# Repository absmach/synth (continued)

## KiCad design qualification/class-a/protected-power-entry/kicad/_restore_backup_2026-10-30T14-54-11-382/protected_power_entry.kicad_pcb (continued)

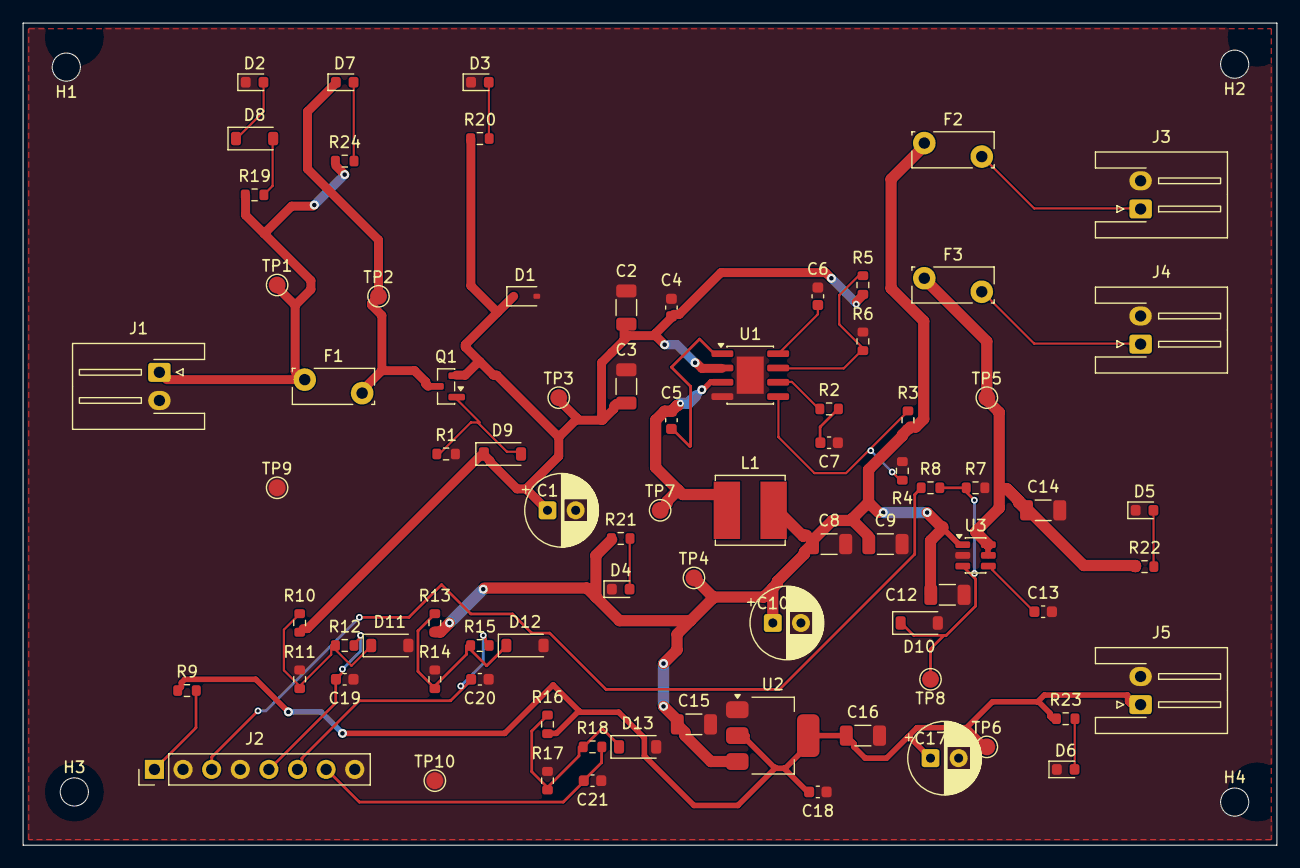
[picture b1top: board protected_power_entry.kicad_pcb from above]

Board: 2 copper layers, 111.3 x 73.0 mm, 84 parts (0 on the bottom side), 34 nets.

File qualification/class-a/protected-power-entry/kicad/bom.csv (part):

refdes,value,kind,description,kicad_symbol,kicad_footprint,lcsc_pn,mpn
C1,100uF 25V,capacitor,"100µF 25V aluminium electrolytic, radial through-hole, polarised",Device:C_Polarized,Capacitor_THT:CP_Radial_D6.3mm_P2.50mm,,
C10,100uF 25V,capacitor,"100µF 25V aluminium electrolytic, radial through-hole, polarised",Device:C_Polarized,Capacitor_THT:CP_Radial_D6.3mm_P2.50mm,,
C12,10uF 10V,capacitor,"Generic 1206 ceramic capacitor, any value",Device:C,Capacitor_SMD:C_1206_3216Metric,,
C13,2.2nF,capacitor,"Generic 0603 MLCC, X7R/X5R, any value",Device:C,Capacitor_SMD:C_0603_1608Metric,,
C14,22uF 10V,capacitor,"Generic 1206 ceramic capacitor, any value",Device:C,Capacitor_SMD:C_1206_3216Metric,,
C15,10uF 10V,capacitor,"Generic 1206 ceramic capacitor, any value",Device:C,Capacitor_SMD:C_1206_3216Metric,,
C16,10uF 10V,capacitor,"Generic 1206 ceramic capacitor, any value",Device:C,Capacitor_SMD:C_1206_3216Metric,,
C17,100uF 25V,capacitor,"100µF 25V aluminium electrolytic, radial through-hole, polarised",Device:C_Polarized,Capacitor_THT:CP_Radial_D6.3mm_P2.50mm,,
C18,100nF,capacitor,"Generic 0603 MLCC, X7R/X5R, any value",Device:C,Capacitor_SMD:C_0603_1608Metric,,
C19,100nF,capacitor,"Generic 0603 MLCC, X7R/X5R, any value",Device:C,Capacitor_SMD:C_0603_1608Metric,,
C2,10uF 25V,capacitor,"Generic 1206 ceramic capacitor, any value",Device:C,Capacitor_SMD:C_1206_3216Metric,,
C20,100nF,capacitor,"Generic 0603 MLCC, X7R/X5R, any value",Device:C,Capacitor_SMD:C_0603_1608Metric,,
C21,100nF,capacitor,"Generic 0603 MLCC, X7R/X5R, any value",Device:C,Capacitor_SMD:C_0603_1608Metric,,
C3,10uF 25V,capacitor,"Generic 1206 ceramic capacitor, any value",Device:C,Capacitor_SMD:C_1206_3216Metric,,
C4,100nF,capacitor,"Generic 0603 MLCC, X7R/X5R, any value",Device:C,Capacitor_SMD:C_0603_1608Metric,,
C5,10nF,capacitor,"Generic 0603 MLCC, X7R/X5R, any value",Device:C,Capacitor_SMD:C_0603_1608Metric,,
C6,100nF,capacitor,"Generic 0603 MLCC, X7R/X5R, any value",Device:C,Capacitor_SMD:C_0603_1608Metric,,
C7,2.2nF,capacitor,"Generic 0603 MLCC, X7R/X5R, any value",Device:C,Capacitor_SMD:C_0603_1608Metric,,
C8,22uF 10V,capacitor,"Generic 1206 ceramic capacitor, any value",Device:C,Capacitor_SMD:C_1206_3216Metric,,
C9,22uF 10V,capacitor,"Generic 1206 ceramic capacitor, any value",Device:C,Capacitor_SMD:C_1206_3216Metric,,
D1,(no value),diode,"5V unidirectional TVS diode, SOD-123 — ESD protection",Device:D_TVS,Diode_SMD:D_SOD-323,,
D10,(no value),diode,"5.1V Zener diode, SOD-123",Device:D_Zener,Diode_SMD:D_SOD-123,,
D11,BZT52C3V3,diode,"BZT52C3V3 3.3 V +/-5 % 500 mW zener diode, SOD-123 (clamp for the ADC sample lines). Vz 3.1 to 3.5 V (nominal 3.3 V) at Izt 5 mA; check against the Diodes Inc. datasheet. No LCSC number asserted.",Device:D_Zener,Diode_SMD:D_SOD-123,,BZT52C3V3
D12,BZT52C3V3,diode,"BZT52C3V3 3.3 V +/-5 % 500 mW zener diode, SOD-123 (clamp for the ADC sample lines). Vz 3.1 to 3.5 V (nominal 3.3 V) at Izt 5 mA; check against the Diodes Inc. datasheet. No LCSC number asserted.",Device:D_Zener,Diode_SMD:D_SOD-123,,BZT52C3V3
D13,BZT52C3V3,diode,"BZT52C3V3 3.3 V +/-5 % 500 mW zener diode, SOD-123 (clamp for the ADC sample lines). Vz 3.1 to 3.5 V (nominal 3.3 V) at Izt 5 mA; check against the Diodes Inc. datasheet. No LCSC number asserted.",Device:D_Zener,Diode_SMD:D_SOD-123,,BZT52C3V3
D2,(no value),diode,"White surface-mount LED, 0603",Device:LED,LED_SMD:LED_0603_1608Metric,,
D3,(no value),diode,"Blue surface-mount LED, 0603",Device:LED,LED_SMD:LED_0603_1608Metric,,
D4,LTST-C190KGKT,diode,"Lite-On LTST-C190KGKT green AlInGaP LED, 0603, Vf 1.9 to 2.4V at 20mA",Device:LED,LED_SMD:LED_0603_1608Metric,,LTST-C190KGKT
D5,0603-GREEN,diode,"Green LED, 0603 package, ~2.2V Vf",Device:LED,LED_SMD:LED_0603_1608Metric,C72043,0603-GREEN
D6,(no value),diode,"Amber surface-mount LED, 0603",Device:LED,LED_SMD:LED_0603_1608Metric,,
D7,LTST-C190KRKT,diode,"Lite-On LTST-C190KRKT red AlInGaP LED, 0603, Vf 1.6 to 2.4V at 20mA",Device:LED,LED_SMD:LED_0603_1608Metric,,LTST-C190KRKT
D8,1N5819HW-7-F,diode,"Diodes Inc. 1N5819HW-7-F, 40 V 1 A Schottky diode, SOD-123, low forward voltage",Device:D_Schottky,Diode_SMD:D_SOD-123,C82544,1N5819HW-7-F
D9,(no value),diode,"5.1V Zener diode, SOD-123",Device:D_Zener,Diode_SMD:D_SOD-123,,
F1,(no value),fuse,"Resettable polyfuse (PPTC), 2-pin",Device:Polyfuse,Fuse:Fuse_Bourns_MF-RG300,,
F2,(no value),fuse,"Resettable polyfuse (PPTC), 2-pin",Device:Polyfuse,Fuse:Fuse_Bourns_MF-RG300,,
F3,(no value),fuse,"Resettable polyfuse (PPTC), 2-pin",Device:Polyfuse,Fuse:Fuse_Bourns_MF-RG300,,
H1,(no value),mounting_hole,M2.5 non-plated mounting hole (NPTH) for a board corner,Mechanical:MountingHole,MountingHole:MountingHole_2.5mm,,
H2,(no value),mounting_hole,M2.5 non-plated mounting hole (NPTH) for a board corner,Mechanical:MountingHole,MountingHole:MountingHole_2.5mm,,
H3,(no value),mounting_hole,M2.5 non-plated mounting hole (NPTH) for a board corner,Mechanical:MountingHole,MountingHole:MountingHole_2.5mm,,
H4,(no value),mounting_hole,M2.5 non-plated mounting hole (NPTH) for a board corner,Mechanical:MountingHole,MountingHole:MountingHole_2.5mm,,
J1,(no value),connector,"JST XH-series 2-pin wire-to-board connector, 2.0mm pitch",Connector_Generic:Conn_01x02,Connector_JST:JST_XH_S2B-XH-A-1_1x02_P2.50mm_Horizontal,,
J2,M20-9990846,connector,"Harwin M20-9990846 1x8 through-hole pin header, 2.54 mm pitch, vertical, 3 A per contact",Connector_Generic:Conn_01x08,Connector_PinHeader_2.54mm:PinHeader_1x08_P2.54mm_Vertical,,M20-9990846
J3,(no value),connector,"JST XH-series 2-pin wire-to-board connector, 2.0mm pitch",Connector_Generic:Conn_01x02,Connector_JST:JST_XH_S2B-XH-A-1_1x02_P2.50mm_Horizontal,,
J4,(no value),connector,"JST XH-series 2-pin wire-to-board connector, 2.0mm pitch",Connector_Generic:Conn_01x02,Connector_JST:JST_XH_S2B-XH-A-1_1x02_P2.50mm_Horizontal,,
J5,(no value),connector,"JST XH-series 2-pin wire-to-board connector, 2.0mm pitch",Connector_Generic:Conn_01x02,Connector_JST:JST_XH_S2B-XH-A-1_1x02_P2.50mm_Horizontal,,
L1,SRN6045TA-100M,inductor,"Bourns SRN6045TA-100M 10 uH semi-shielded power inductor, 6.0x6.0x4.2 mm. Datasheet at 25 C: DCR 52 mOhm +/-20 %, Irms 3.2 A (40 C rise), Isat 4.6 A (30 % inductance drop), SRF 25 MHz.",Device:L,Inductor_SMD:L_Bourns_SRN6045TA,,SRN6045TA-100M
Q1,(no value),transistor,"Vishay Si2301 P-channel power MOSFET, SOT-23",Transistor_FET:Si2301CDS,Package_TO_SOT_SMD:SOT-23,,
R1,47k,resistor,"Generic 0603 thick-film resistor, any value",Device:R_US,Resistor_SMD:R_0603_1608Metric,,
R10,10k,resistor,"Generic 0603 thick-film resistor, any value",Device:R_US,Resistor_SMD:R_0603_1608Metric,,
R11,2k,resistor,"Generic 0603 thick-film resistor, any value",Device:R_US,Resistor_SMD:R_0603_1608Metric,,
R12,1k,resistor,"Generic 0603 thick-film resistor, any value",Device:R_US,Resistor_SMD:R_0603_1608Metric,,
R13,10k,resistor,"Generic 0603 thick-film resistor, any value",Device:R_US,Resistor_SMD:R_0603_1608Metric,,
R14,10k,resistor,"Generic 0603 thick-film resistor, any value",Device:R_US,Resistor_SMD:R_0603_1608Metric,,
R15,1k,resistor,"Generic 0603 thick-film resistor, any value",Device:R_US,Resistor_SMD:R_0603_1608Metric,,
R16,10k,resistor,"Generic 0603 thick-film resistor, any value",Device:R_US,Resistor_SMD:R_0603_1608Metric,,
R17,10k,resistor,"Generic 0603 thick-film resistor, any value",Device:R_US,Resistor_SMD:R_0603_1608Metric,,
R18,1k,resistor,"Generic 0603 thick-film resistor, any value",Device:R_US,Resistor_SMD:R_0603_1608Metric,,
R19,3k,resistor,"Generic 0603 thick-film resistor, any value",Device:R_US,Resistor_SMD:R_0603_1608Metric,,
R2,10k,resistor,"Generic 0603 thick-film resistor, any value",Device:R_US,Resistor_SMD:R_0603_1608Metric,,
R20,3.3k,resistor,"Generic 0603 thick-film resistor, any value",Device:R_US,Resistor_SMD:R_0603_1608Metric,,
R21,1k,resistor,"Generic 0603 thick-film resistor, any value",Device:R_US,Resistor_SMD:R_0603_1608Metric,,
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
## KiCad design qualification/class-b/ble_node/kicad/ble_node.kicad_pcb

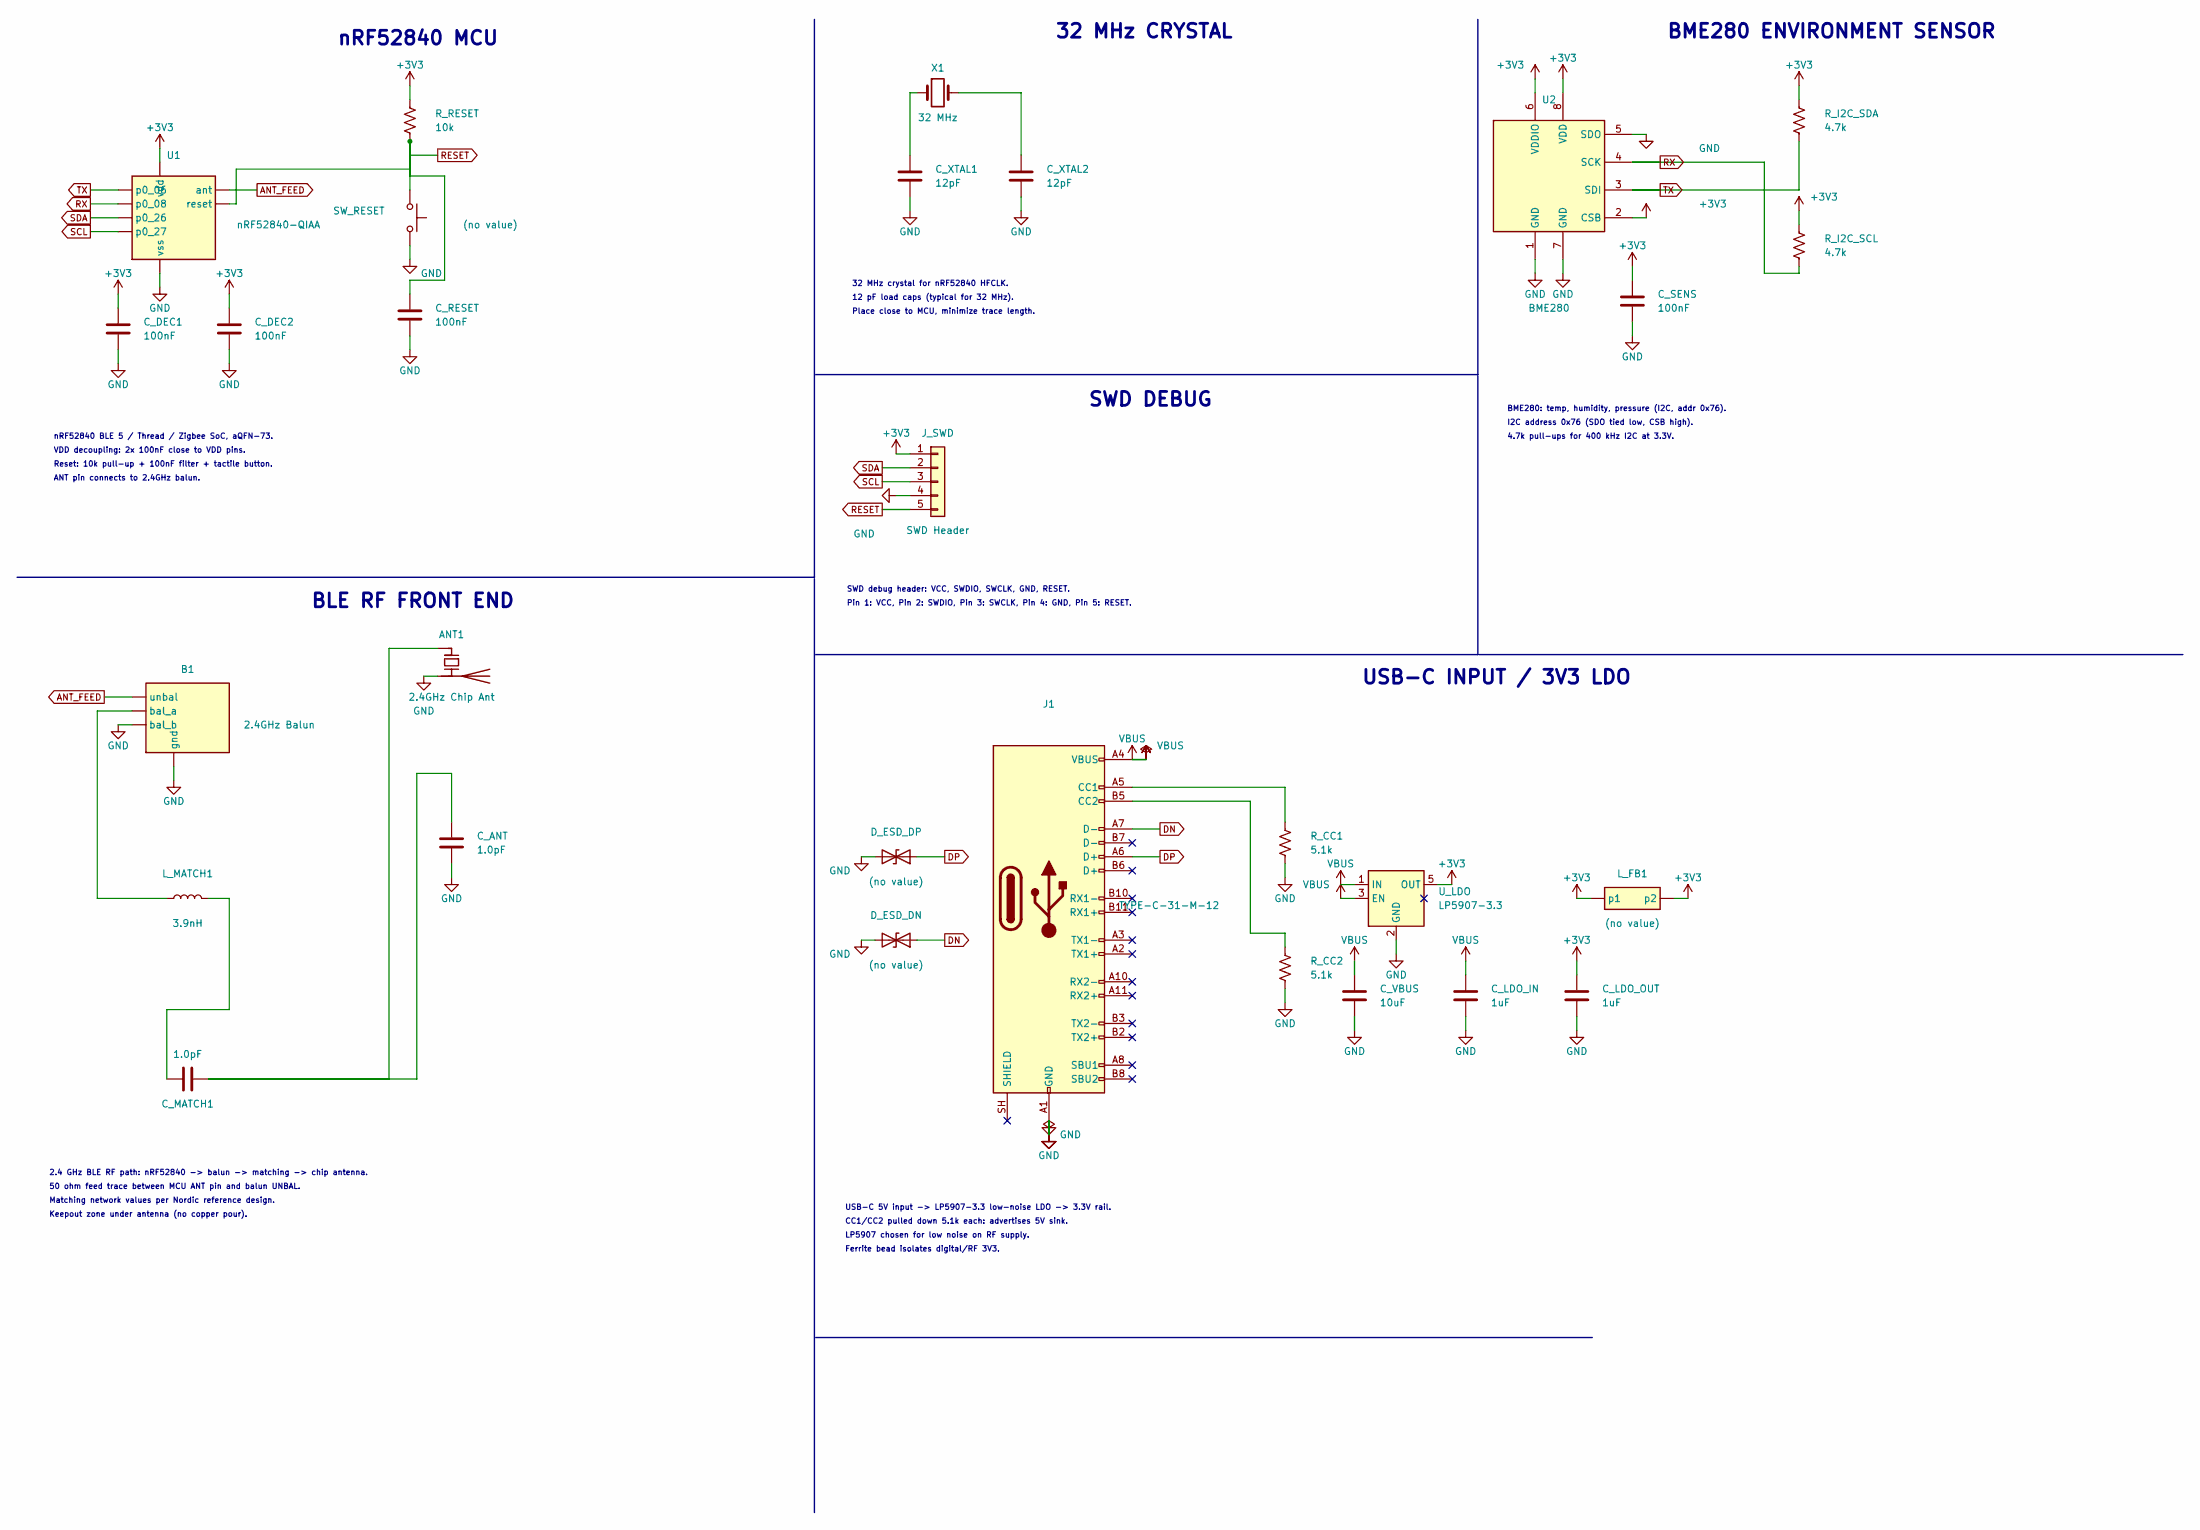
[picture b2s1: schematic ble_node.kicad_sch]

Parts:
ANT1: 2.4GHz Chip Ant; Johanson_2450AT43F0100; MPN 2450AT43F0100E; LCSC C17192881
B1: 2.4GHz Balun; Balun_Johanson_0896BM15A0001; MPN 2450BL15B100
C_ANT: 1.0pF; C_0402_1005Metric
C_DEC1, C_DEC2: 100nF; C_0603_1608Metric
C_LDO_IN: 1uF; C_0603_1608Metric
C_LDO_OUT: 1uF; C_0603_1608Metric
C_MATCH1: 1.0pF; C_0402_1005Metric
C_RESET: 100nF; C_0603_1608Metric
C_SENS: 100nF; C_0603_1608Metric
C_VBUS: 10uF; C_0805_2012Metric
C_XTAL1, C_XTAL2: 12pF; C_0603_1608Metric
D_ESD_DN: (no value); D_SOD-323
D_ESD_DP: (no value); D_SOD-323
J1: TYPE-C-31-M-12; USB_C_Receptacle_HRO_TYPE-C-31-M-12; MPN TYPE-C-31-M-12; LCSC C165948
J_SWD: SWD Header; PinHeader_1x05_P2.54mm_Vertical
L_FB1: (no value); L_0603_1608Metric
L_MATCH1: 3.9nH; L_0402_1005Metric
R_CC1, R_CC2: 5.1k; R_0603_1608Metric
R_I2C_SCL, R_I2C_SDA: 4.7k; R_0603_1608Metric
R_RESET: 10k; R_0603_1608Metric
SW_RESET: (no value); SW_SPST_PTS645Sx43SMTR92
U1: nRF52840-QIAA; Nordic_AQFN-73-1EP_7x7mm_P0.5mm; MPN NRF52840-QIAA-R; LCSC C190794
U2: BME280; Bosch_LGA-8_2.5x2.5mm_P0.65mm_ClockwisePinNumbering; MPN BME280; LCSC C92489
U_LDO: LP5907-3.3; SOT-23-5; MPN LP5907MFX-3.3; LCSC C83437
X1: 32 MHz; Crystal_SMD_3225-4Pin_3.2x2.5mm

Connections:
+3V3: C_DEC1.1, C_DEC2.1, C_LDO_OUT.1, C_SENS.1, J_SWD.1, L_FB1.1 (p1), L_FB1.2 (p2), R_I2C_SCL.2, R_I2C_SDA.2, R_RESET.1, U1.A22 (vdd), U2.2 (CSB), U2.6 (VDDIO), U2.8 (VDD), U_LDO.5 (OUT)
ANT_FEED: B1.1 (unbal), U1.H23 (ant)
GND: ANT1.2 (PCB_Trace), B1.3 (bal_b), B1.4 (gnd), C_ANT.2, C_DEC1.2, C_DEC2.2, C_LDO_IN.2, C_LDO_OUT.2, C_RESET.2, C_SENS.2, C_VBUS.2, C_XTAL1.2, C_XTAL2.2, D_ESD_DN.2 (A2), D_ESD_DP.2 (A2), J1.A1 (GND), J1.A12 (GND), J1.B1 (GND), J1.B12 (GND), J1.SH (SHIELD), J_SWD.4, R_CC1.2, R_CC2.2, SW_RESET.2, U1.B7 (vss), U2.1 (GND), U2.5 (SDO), U2.7 (GND), U_LDO.2 (GND)
net_0: C_LDO_IN.1, C_VBUS.1, J1.A4 (VBUS), J1.A9 (VBUS), J1.B4 (VBUS), J1.B9 (VBUS), U_LDO.1 (IN), U_LDO.3 (EN)
net_3: J1.A5 (CC1), R_CC1.1
net_4: J1.B5 (CC2), R_CC2.1
net_5: D_ESD_DP.1 (A1), J1.A6 (D+), J1.B6 (D+)
net_6: D_ESD_DN.1 (A1), J1.A7 (D-), J1.B7 (D-)
net_7: C_RESET.1, J_SWD.5, R_RESET.2, SW_RESET.1, U1.AC13 (reset)
net_8: C_XTAL1.1, X1.1
net_9: C_XTAL2.1, X1.2
net_10: B1.2 (bal_a), L_MATCH1.1
net_11: C_MATCH1.1, L_MATCH1.2
net_12: ANT1.1 (FEED), C_ANT.1, C_MATCH1.2
net_13: R_I2C_SDA.1, U1.L1 (p0_06), U2.3 (SDI)
net_14: R_I2C_SCL.1, U1.N1 (p0_08), U2.4 (SCK)
net_15: J_SWD.2, U1.G1 (p0_26)
net_16: J_SWD.3, U1.H2 (p0_27)

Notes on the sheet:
USB-C INPUT / 3V3 LDO
nRF52840 MCU
32 MHz CRYSTAL
BLE RF FRONT END
BME280 ENVIRONMENT SENSOR
SWD DEBUG
USB-C 5V input -> LP5907-3.3 low-noise LDO -> 3.3V rail.
CC1/CC2 pulled down 5.1k each: advertises 5V sink.
LP5907 chosen for low noise on RF supply.
Ferrite bead isolates digital/RF 3V3.
nRF52840 BLE 5 / Thread / Zigbee SoC, aQFN-73.
VDD decoupling: 2x 100nF close to VDD pins.
Reset: 10k pull-up + 100nF filter + tactile button.
ANT pin connects to 2.4GHz balun.
32 MHz crystal for nRF52840 HFCLK.
12 pF load caps (typical for 32 MHz).
Place close to MCU, minimize trace length.
2.4 GHz BLE RF path: nRF52840 -> balun -> matching -> chip antenna.
50 ohm feed trace between MCU ANT pin and balun UNBAL.
Matching network values per Nordic reference design.
Keepout zone under antenna (no copper pour).
BME280: temp, humidity, pressure (I2C, addr 0x76).
I2C address 0x76 (SDO tied low, CSB high).
4.7k pull-ups for 400 kHz I2C at 3.3V.
SWD debug header: VCC, SWDIO, SWCLK, GND, RESET.
Pin 1: VCC, Pin 2: SWDIO, Pin 3: SWCLK, Pin 4: GND, Pin 5: RESET.

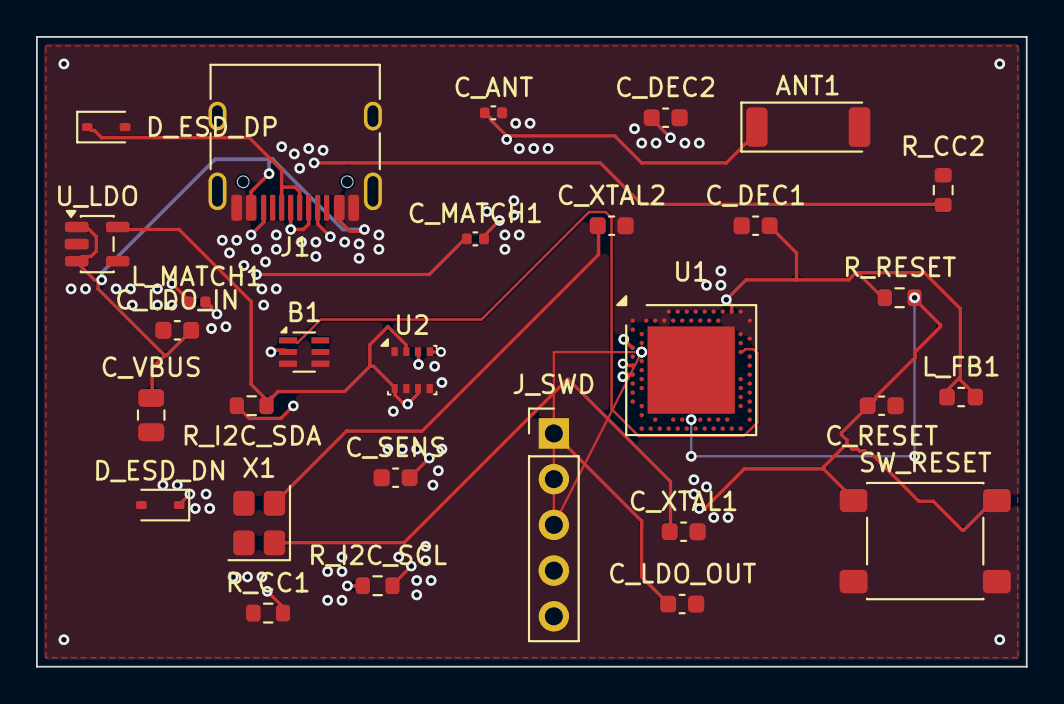
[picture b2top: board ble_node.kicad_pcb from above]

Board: 4 copper layers, 55.0 x 35.0 mm, 29 parts (0 on the bottom side), 18 nets.

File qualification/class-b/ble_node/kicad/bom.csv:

refdes,value,kind,description,kicad_symbol,kicad_footprint,lcsc_pn,mpn
ANT1,2.4GHz Chip Ant,antenna,"Ceramic chip antenna, 2.4 GHz, 1 dBi, SMD",Device:Antenna_Chip,RF_Antenna:Johanson_2450AT43F0100,C17192881,2450AT43F0100E
B1,2.4GHz Balun,filter,"2.4 GHz balun + matching network, integrated SMD",RF_Module:balun_2g4,RF_Converter:Balun_Johanson_0896BM15A0001,,2450BL15B100
C_ANT,1.0pF,capacitor,"Generic 0402 MLCC, X7R/X5R, any value",Device:C,Capacitor_SMD:C_0402_1005Metric,,
C_DEC1,100nF,capacitor,"Generic 0603 MLCC, X7R/X5R, any value",Device:C,Capacitor_SMD:C_0603_1608Metric,,
C_DEC2,100nF,capacitor,"Generic 0603 MLCC, X7R/X5R, any value",Device:C,Capacitor_SMD:C_0603_1608Metric,,
C_LDO_IN,1uF,capacitor,"Generic 0603 MLCC, X7R/X5R, any value",Device:C,Capacitor_SMD:C_0603_1608Metric,,
C_LDO_OUT,1uF,capacitor,"Generic 0603 MLCC, X7R/X5R, any value",Device:C,Capacitor_SMD:C_0603_1608Metric,,
C_MATCH1,1.0pF,capacitor,"Generic 0402 MLCC, X7R/X5R, any value",Device:C,Capacitor_SMD:C_0402_1005Metric,,
C_RESET,100nF,capacitor,"Generic 0603 MLCC, X7R/X5R, any value",Device:C,Capacitor_SMD:C_0603_1608Metric,,
C_SENS,100nF,capacitor,"Generic 0603 MLCC, X7R/X5R, any value",Device:C,Capacitor_SMD:C_0603_1608Metric,,
C_VBUS,10uF,capacitor,"Generic 0805 MLCC, X7R/X5R, any value",Device:C,Capacitor_SMD:C_0805_2012Metric,,
C_XTAL1,12pF,capacitor,"Generic 0603 MLCC, X7R/X5R, any value",Device:C,Capacitor_SMD:C_0603_1608Metric,,
C_XTAL2,12pF,capacitor,"Generic 0603 MLCC, X7R/X5R, any value",Device:C,Capacitor_SMD:C_0603_1608Metric,,
D_ESD_DN,(no value),diode,"USB-line ESD protection (TVS diode array), bidirectional",Device:D_TVS,Diode_SMD:D_SOD-323,,
D_ESD_DP,(no value),diode,"USB-line ESD protection (TVS diode array), bidirectional",Device:D_TVS,Diode_SMD:D_SOD-323,,
J1,TYPE-C-31-M-12,connector,"USB-C receptacle, 24-pin SMD. Modelled here with primary and mirrored power/ground/data pins for full pad coverage.",Connector:USB_C_Receptacle,Connector_USB:USB_C_Receptacle_HRO_TYPE-C-31-M-12,C165948,TYPE-C-31-M-12
J_SWD,SWD Header,connector,"1x5 through-hole pin header, 2.54 mm pitch (SWD); datasheet_url is the product page of the Harwin M20 series, no manufacturer PDF link was verifiable",Connector_Generic:Conn_01x05,Connector_PinHeader_2.54mm:PinHeader_1x05_P2.54mm_Vertical,,
L_FB1,(no value),inductor,"0603 ferrite bead, 600Ω @ 100MHz — EMI suppression",Device:Ferrite_Bead,Inductor_SMD:L_0603_1608Metric,,
L_MATCH1,3.9nH,inductor,"Generic 0402 wirewound inductor, any value",Device:L,Inductor_SMD:L_0402_1005Metric,,
R_CC1,5.1k,resistor,"Generic 0603 thick-film resistor, any value",Device:R_US,Resistor_SMD:R_0603_1608Metric,,
R_CC2,5.1k,resistor,"Generic 0603 thick-film resistor, any value",Device:R_US,Resistor_SMD:R_0603_1608Metric,,
R_I2C_SCL,4.7k,resistor,"Generic 0603 thick-film resistor, any value",Device:R_US,Resistor_SMD:R_0603_1608Metric,,
R_I2C_SDA,4.7k,resistor,"Generic 0603 thick-film resistor, any value",Device:R_US,Resistor_SMD:R_0603_1608Metric,,
R_RESET,10k,resistor,"Generic 0603 thick-film resistor, any value",Device:R_US,Resistor_SMD:R_0603_1608Metric,,
SW_RESET,(no value),switch,Generic SPST tactile button,Switch:SW_Push,Button_Switch_SMD:SW_SPST_PTS645Sx43SMTR92,,
U1,nRF52840-QIAA,mcu,"Nordic nRF52840 ARM Cortex-M4F with BLE 5/Thread/Zigbee, aQFN-73 7x7mm",RF_Module:NRF52840-QIAA,Package_DFN_QFN:Nordic_AQFN-73-1EP_7x7mm_P0.5mm,C190794,NRF52840-QIAA-R
U2,BME280,sensor,"Bosch BME280 temperature/humidity/pressure sensor, I2C/SPI",Sensor:BME280,Package_LGA:Bosch_LGA-8_2.5x2.5mm_P0.65mm_ClockwisePinNumbering,C92489,BME280
U_LDO,LP5907-3.3,regulator,"TI LP5907 3.3V low-noise LDO, 250mA, SOT-23-5",Regulator_Linear:LP5907MFX-3.3,Package_TO_SOT_SMD:SOT-23-5,C83437,LP5907MFX-3.3
X1,32 MHz,crystal,"Generic quartz crystal, 2-pin SMD",Device:Crystal,Crystal:Crystal_SMD_3225-4Pin_3.2x2.5mm,,

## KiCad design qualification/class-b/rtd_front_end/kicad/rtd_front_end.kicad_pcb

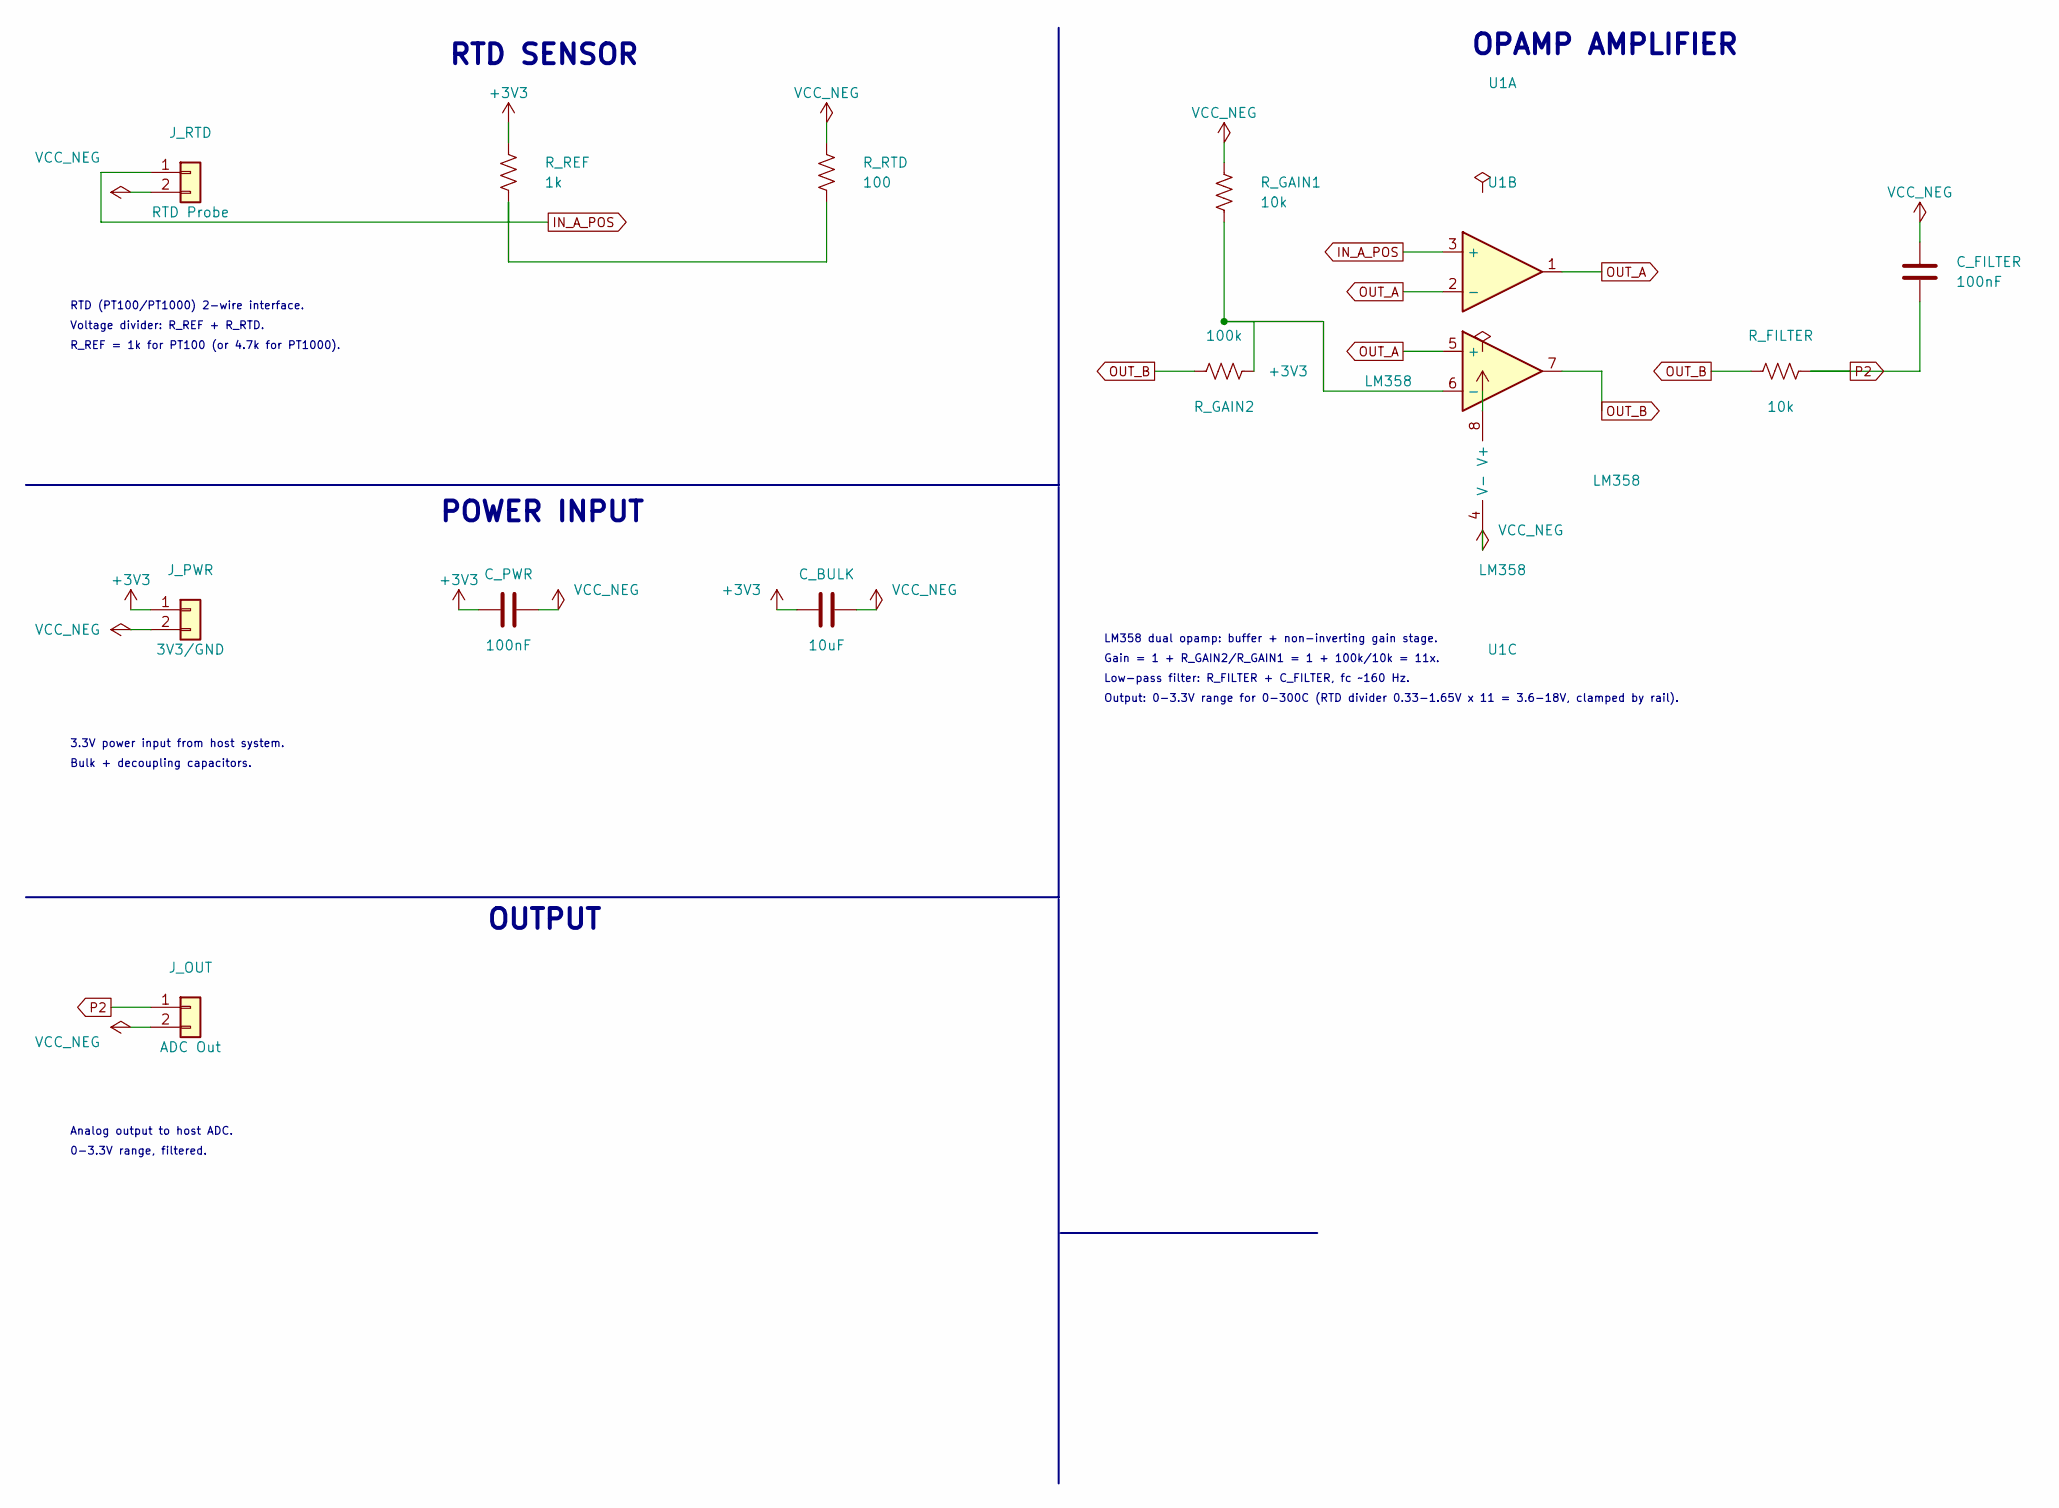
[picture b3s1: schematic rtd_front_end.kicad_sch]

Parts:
C_BULK: 10uF; C_0805_2012Metric
C_FILTER: 100nF; C_0603_1608Metric
C_PWR: 100nF; C_0603_1608Metric
J_OUT: ADC Out; PinHeader_1x02_P2.54mm_Vertical; MPN HX PZ2.54-1x2P ZZ; LCSC C32713268
J_PWR: 3V3/GND; PinHeader_1x02_P2.54mm_Vertical; MPN HX PZ2.54-1x2P ZZ; LCSC C32713268
J_RTD: RTD Probe; PinHeader_1x02_P2.54mm_Vertical; MPN HX PZ2.54-1x2P ZZ; LCSC C32713268
R_FILTER: 10k; R_0603_1608Metric
R_GAIN1: 10k; R_0603_1608Metric
R_GAIN2: 100k; R_0603_1608Metric
R_REF: 1k; R_0603_1608Metric
R_RTD: 100; R_0603_1608Metric
U1: LM358; DIP-8_W7.62mm

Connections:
GND: C_BULK.2, C_FILTER.2, C_PWR.2, J_OUT.2, J_PWR.2, J_RTD.2, R_GAIN1.2, R_RTD.2, U1.4 (V-); also elsewhere on the board
net_0: C_BULK.1, C_PWR.1, J_PWR.1, R_REF.1, U1.8 (V+)
net_2: J_RTD.1, R_REF.2, R_RTD.1, U1.3 (+); also elsewhere on the board
net_3: U1.1, U1.2 (-), U1.5 (+)
net_4: R_GAIN1.1, R_GAIN2.1, U1.6 (-)
net_5: R_FILTER.1, R_GAIN2.2, U1.7
net_6: C_FILTER.1, J_OUT.1, R_FILTER.2

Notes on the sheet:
POWER INPUT
RTD SENSOR
OPAMP AMPLIFIER
OUTPUT
3.3V power input from host system.
Bulk + decoupling capacitors.
RTD (PT100/PT1000) 2-wire interface.
Voltage divider: R_REF + R_RTD.
R_REF = 1k for PT100 (or 4.7k for PT1000).
LM358 dual opamp: buffer + non-inverting gain stage.
Gain = 1 + R_GAIN2/R_GAIN1 = 1 + 100k/10k = 11x.
Low-pass filter: R_FILTER + C_FILTER, fc ~160 Hz.
Output: 0-3.3V range for 0-300C (RTD divider 0.33-1.65V x 11 = 3.6-18V, clamped by rail).
Analog output to host ADC.
0-3.3V range, filtered.

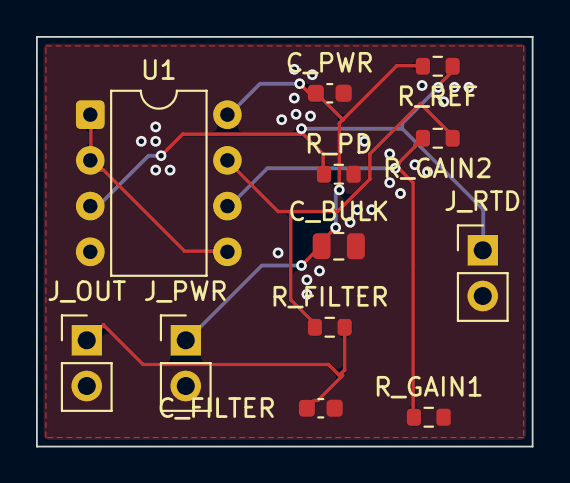
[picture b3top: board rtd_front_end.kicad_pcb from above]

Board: 2 copper layers, 27.5 x 22.8 mm, 12 parts (0 on the bottom side), 7 nets.

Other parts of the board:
R_PD: 100k; R_0603_1608Metric

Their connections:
GND: R_PD.2; also elsewhere on the board
net_2: R_PD.1; also elsewhere on the board
